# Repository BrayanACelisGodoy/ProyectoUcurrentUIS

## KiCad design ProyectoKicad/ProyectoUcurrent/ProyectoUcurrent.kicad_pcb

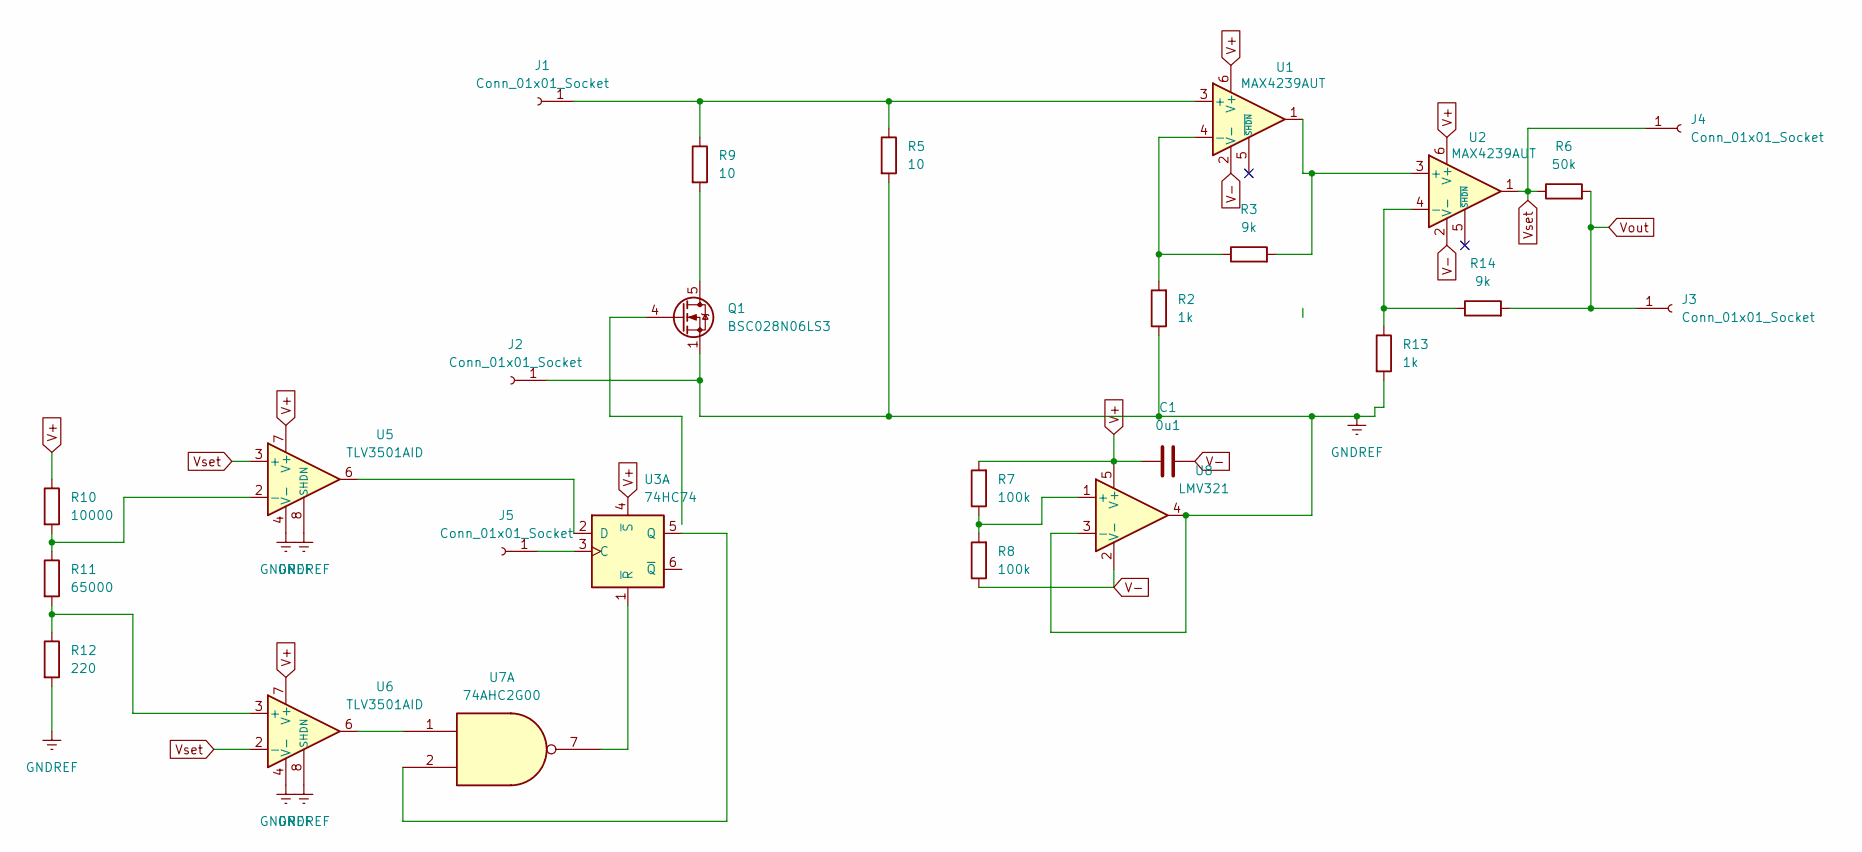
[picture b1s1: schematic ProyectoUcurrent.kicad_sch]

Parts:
C1: 0u1; CP_Elec_3x5.3
J1, J2, J3, J4, J5: Conn_01x01_Socket; SolderWire-1.5sqmm_1x01_D1.7mm_OD3mm
Q1: BSC028N06LS3; TDSON-8-1
R2, R13: 1k; R_Axial_DIN0414_L11.9mm_D4.5mm_P25.40mm_Horizontal
R3, R14: 9k; R_Axial_DIN0414_L11.9mm_D4.5mm_P25.40mm_Horizontal
R5, R9: 10; R_Axial_DIN0414_L11.9mm_D4.5mm_P25.40mm_Horizontal
R6: 50k; R_Axial_DIN0414_L11.9mm_D4.5mm_P25.40mm_Horizontal
R7, R8: 100k; R_Axial_DIN0414_L11.9mm_D4.5mm_P25.40mm_Horizontal
R10: 10000; R_Axial_DIN0414_L11.9mm_D4.5mm_P25.40mm_Horizontal
R11: 65000; R_Axial_DIN0414_L11.9mm_D4.5mm_P25.40mm_Horizontal
R12: 220; R_Axial_DIN0414_L11.9mm_D4.5mm_P25.40mm_Horizontal
U1, U2: MAX4239AUT; SOT-23-6
U3: 74HC74; DIP-14_W7.62mm
U5, U6: TLV3501AID; SOIC-8_3.9x4.9mm_P1.27mm
U7: 74AHC2G00; SSOP-8_2.95x2.8mm_P0.65mm
U8: LMV321; SOT-23-5

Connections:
GNDREF: J2.1, Q1.1 (S), Q1.2 (S), Q1.3 (S), R2.1, R5.2, R12.2, R13.2, U5.4 (V-), U5.8 (SHDN), U6.4 (V-), U6.8 (SHDN), U8.3 (-), U8.4
unnamed: J1.1, R5.1, R9.1, U1.3 (+)
unnamed: J5.1, U3.3 (C)
unnamed: Q1.5 (D), R9.2
unnamed: R2.2, R3.1, U1.4 (-)
unnamed: R3.2, U1.1, U2.3 (+)
unnamed: R13.1, R14.1, U2.4 (-)
unnamed: U3.2 (D), U5.6
unnamed: U3.5 (Q), U7.2
unnamed: U3.1 (~R), U7.7
unnamed: R10.2, R11.1, U5.2 (-)
unnamed: R11.2, R12.1, U6.3 (+)
unnamed: U6.6, U7.1
unnamed: R7.1, R8.2, U8.1 (+)
V+: C1.1, R7.2, R10.1, U1.6 (V+), U2.6 (V+), U3.4 (~S), U5.7 (V+), U6.7 (V+), U8.5 (V+)
V-: C1.2, R8.1, U1.2 (V-), U2.2 (V-), U8.2 (V-)
Vout: J3.1, R6.2, R14.2
Vset: J4.1, R6.1, U2.1, U5.3 (+), U6.2 (-)

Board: 2 copper layers, 26 parts (0 on the bottom side), 18 nets, no tracks yet.

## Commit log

2024-09-27 Meme
    MemePrueba1
2024-09-27 Revert "Initial commit"
    This reverts commit 5c0491f74e25ec2df326ee752bc3347a00638a32.
2024-09-27 Revert "Meme"
    This reverts commit 7f4a04ff8e2a52f2cc741d9f3f0db55a3646feff.
2024-09-27 Reapply "Initial commit"
    This reverts commit 0fd2651cf4dfcaedd1c5525abca7450c85220472.
2024-09-27 Reapply "Meme"
    This reverts commit 403de4f1dff8d91a4777e47a3a310ec02215194f.
2024-09-27 Brayan
    Añadida de la simulacion del sistema medior de corriente
2024-09-27 DiseñoComparador
    Circuito de comparacion agregado para pruebas
2024-09-27 CambiosComparador
    Cambios En el sistema de comparacion con el lm358 en umbrales bajos funcional para que den la salida
2024-09-27 creacion documento de texto
2024-09-27 SeleccionMosfetConmutacion
    Se comprobo la simulacion del irlz44n que funciona para la conmutacion necesaria
2024-09-27 Cambios_al_Mosfet_Conmutador_Circuito
    se agrego el mosfet de conmutacion al circuito completo se espera simulacion en proteus
2024-09-27 Cambios_Mosfet2
2024-09-27 IniciosCreacionCargadorBateria
    Se empieza a crear las pruebas de cargador pero no funciona
2024-09-27 CreacionProyectoEnProteus
    Se crea la simulacion inicial del proyecto en proteus para simulacion completa
2024-09-27 Proteus Cambios2
2024-09-27 ParcialRedes
2024-09-27 GuardadosCambiosParcial
2024-09-28 CONTROLESpARCIAL
2024-09-28 FinalizacionParcial
2024-09-28 EliminacionElementosParcialRedes
2024-09-30 SimOP
    Se simulo en ltspice y se hico en operal y funciona en ciertos rangos pero explota en algunos
2024-09-30 Simulaciones Probadas en orcad
    Se intento simular en orcad pero sin provehco
2024-10-01 se añadio una copia para pruebas ideales
2024-10-03 Cambios
    Cambios en no idealidad y en el comparador
2024-10-04 Cambios cOMPARADOR
2024-10-04 Solucion comparador
2024-10-05 Sistema Comparador
2024-10-06 SistemaComparadorCompletado
2024-10-06 CreacionPCB_Kicad
2024-10-07 CarpetasLabs
2024-10-07 SubidaLibrerias
2024-10-07 CambiosMosfetResisteciaAlta
2024-10-08 Cambios_Modelo_Mosfet
    Se cambio el modelo del mosfet al BSC009N04LS y se introdujo otra fuente de corriente para ver ambas funcionando en micro y milis
2024-10-08 Cambios Requeridos de carpetas
2024-10-09 Independizacion_Latch
2024-10-09 Organizacion
    Se añadio y organizo las carpetas,y se creo el programa de la esp32 para la web
2024-10-09 Elementos Innecesarios Borrados
2024-10-09 AjustesCarpetas
    AjustesCarpetas
2024-10-10 V2_Programa_Esp
    Se realizo una version dos de la aplicacion web en la cual se toma el saber la medicion mediante pines de la placa y no lo controla el rango la esp32s
2024-10-10 updates
    Ltspice tiene el switch 4 puertos,se creo y empezo a desarrollar el informe y
2024-10-10 AjustesCarpetas
    Se borraron carpetas ltspice innecesarias y se hizo el esquematico completo en ltspice
2024-10-10 añadida las librerias de ltspice
2024-10-10 AgregadosPinesEsp
2024-10-10 EsquematicoCompletoPdf
2024-10-10 Update_Informe_Progrma_app
    Programa aplicacion de celular
2024-10-10 CreacionProgramaAndroidStudio
2024-10-11 modulos android
2024-10-11 CreacionProyectoAndroidEstudio
2024-10-11 UpdatesApkCread
2024-10-11 Updates_LightSleepMode
2024-10-12 UpdateInformeHTMl
2024-10-15 updatesSimInforme
2024-10-15 UodateInforme_Sims
2024-10-15 actualizacion informe
2024-10-15 Revert "actualizacion informe"
    This reverts commit 269f99376d0f94af8fce63ecf76e12ac6c535a46.
2024-10-15 Update_Informe
    updateNombres
2024-10-15 CreacionPdfInforme
2024-10-15 AñadidoPCb
2024-10-16 UpdatesInforme
2024-10-16 Organizacion
2024-10-16 update_informee
2024-10-16 OrganizacionFinal
2024-10-16 AñadidosElementosPCB
2024-10-16 UpdateFInal1
2024-10-16 update_final2
2024-10-28 SubidaData
2024-10-30 AñadidaImagenIdeal2
2024-10-30 idk1
2024-10-31 Carpeta de imagenes
2024-10-31 Upfig3
2024-10-31 Add_images
2024-10-31 update informe 2
2024-11-01 organizacion version informe
2024-11-01 updatev3
2024-11-21 update Final?
2024-11-22 update final si o si ahora si porfavor
2024-11-29 updateas
2024-11-29 update informe
